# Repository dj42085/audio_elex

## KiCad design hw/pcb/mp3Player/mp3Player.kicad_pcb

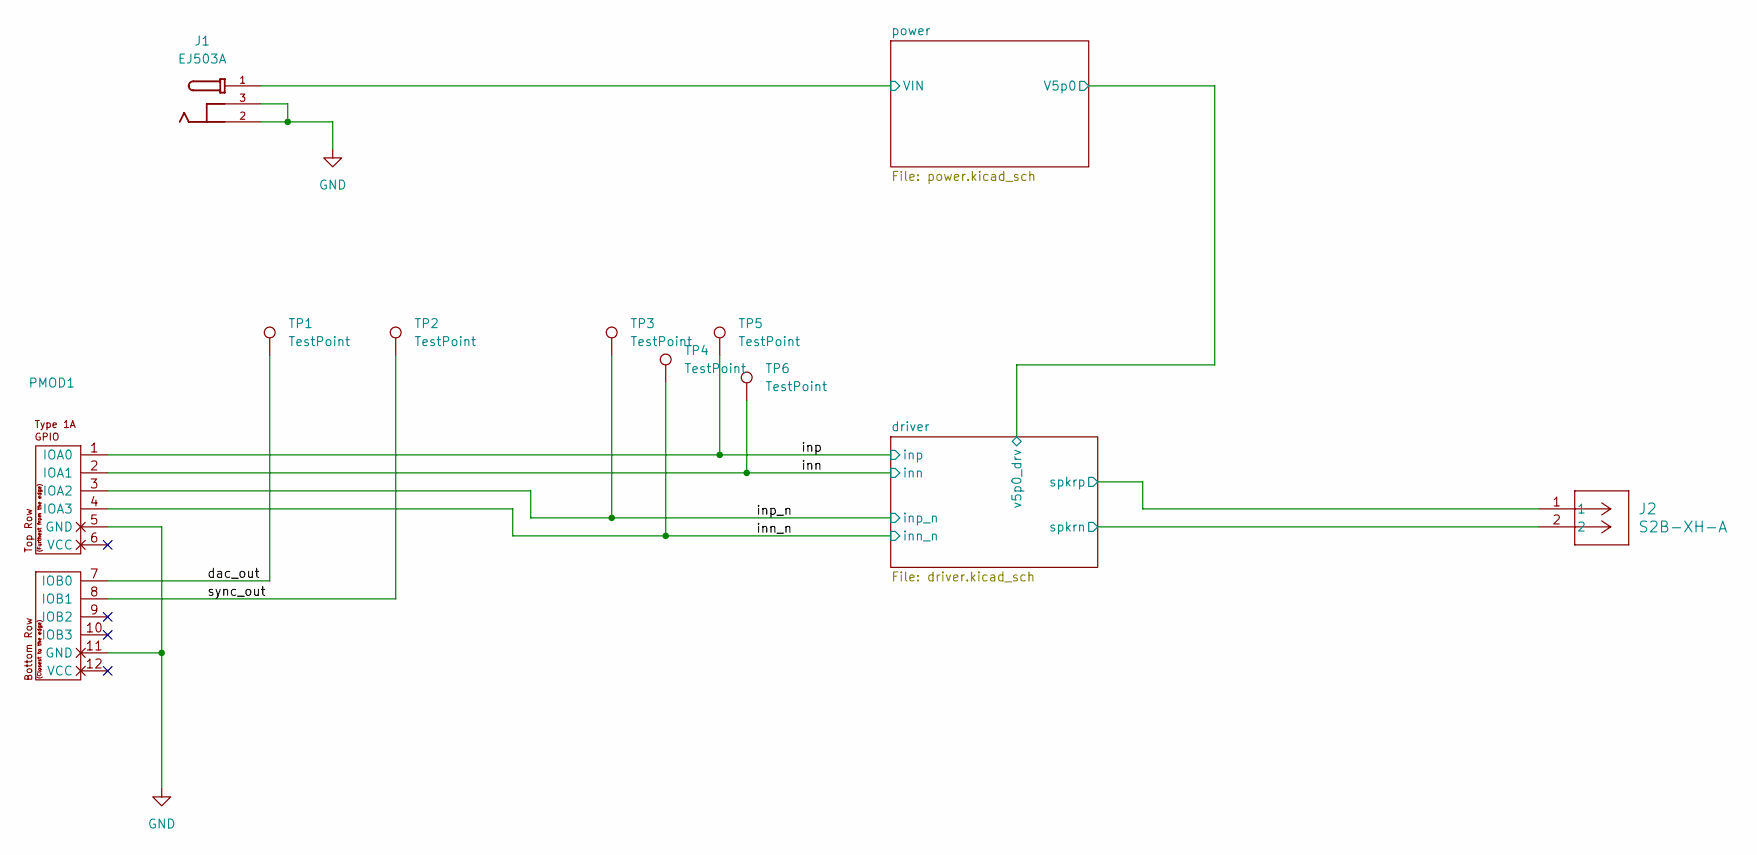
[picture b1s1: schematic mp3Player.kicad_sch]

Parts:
J1: EJ503A; MPD_EJ503A; MPN EJ503A; DigiKey_Part_Number EJ503A-ND
J2: S2B-XH-A; CONN_S2B-XH-A_JST
PMOD1: PMOD-Device-x2-Type-1A-GPIO; pmod_pin_array_6x2
TP1, TP2, TP3, TP4, TP5, TP6: TestPoint; TestPoint_Keystone_5019_Miniature

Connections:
/dac_out: PMOD1.7 (IOB0), TP1.1 (1_1)
/driver/spkrn: J2.2; also elsewhere on the board
/driver/spkrp: J2.1; also elsewhere on the board
/inn: PMOD1.2 (IOA1), TP6.1 (1_1); also elsewhere on the board
/inn_n: PMOD1.4 (IOA3), TP4.1 (1_1); also elsewhere on the board
/inp: PMOD1.1 (IOA0), TP5.1 (1_1); also elsewhere on the board
/inp_n: PMOD1.3 (IOA2), TP3.1 (1_1); also elsewhere on the board
/power/VIN: J1.1; also elsewhere on the board
/sync_out: PMOD1.8 (IOB1), TP2.1 (1_1)
GND: J1.2, J1.3, PMOD1.5 (GND), PMOD1.11 (GND); also elsewhere on the board

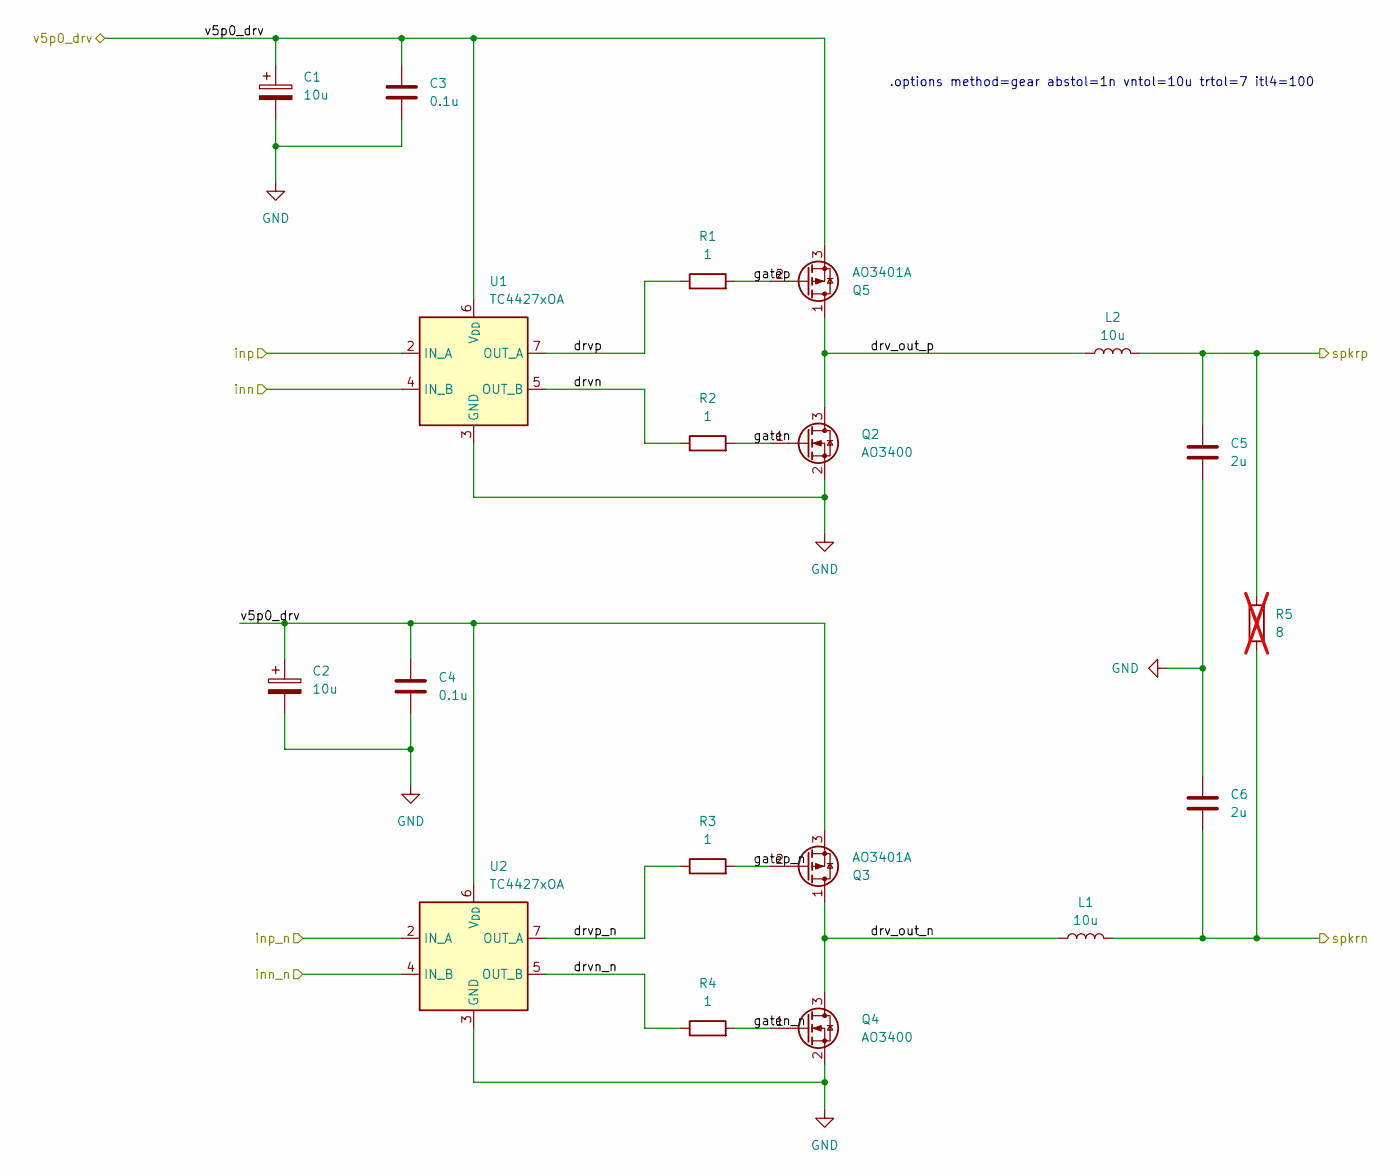
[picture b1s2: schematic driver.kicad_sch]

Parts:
C1, C2: 10u; C_1206_3216Metric
C3, C4: 0.1u; C_0603_1608Metric
C5, C6: 2u; C_0603_1608Metric
L1, L2: 10u; L_Coilcraft_LPS3314
Q2, Q4: AO3400; SOT-23
Q3, Q5: AO3401A; SOT-23
R1, R2, R3, R4: 1; R_0603_1608Metric
R5: 8; not fitted
U1, U2: TC4427xOA; SOIC-8_3.9x4.9mm_P1.27mm

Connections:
/driver/drv_out_n: L1.1, Q3.1 (D), Q4.3 (D)
/driver/drv_out_p: L2.1, Q2.3 (D), Q5.1 (D)
/driver/drvn: R2.1, U1.5 (OUT_B)
/driver/drvn_n: R4.1, U2.5 (OUT_B)
/driver/drvp: R1.1, U1.7 (OUT_A)
/driver/drvp_n: R3.1, U2.7 (OUT_A)
/driver/gaten: Q2.1 (G), R2.2
/driver/gaten_n: Q4.1 (G), R4.2
/driver/gatep: Q5.2 (G), R1.2
/driver/gatep_n: Q3.2 (G), R3.2
/driver/spkrn: C6.2, L1.2, R5.1; also elsewhere on the board
/driver/spkrp: C5.1, L2.2, R5.2; also elsewhere on the board
/driver/v5p0_drv: C1.1, C2.1, C3.1, C4.1, Q3.3 (S), Q5.3 (S), U1.6 (V_{DD}), U2.6 (V_{DD}); also elsewhere on the board
/inn: U1.4 (IN_B); also elsewhere on the board
/inn_n: U2.4 (IN_B); also elsewhere on the board
/inp: U1.2 (IN_A); also elsewhere on the board
/inp_n: U2.2 (IN_A); also elsewhere on the board
GND: C1.2, C2.2, C3.2, C4.2, C5.2, C6.1, Q2.2 (S), Q4.2 (S), U1.3 (GND), U2.3 (GND); also elsewhere on the board

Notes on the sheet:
.options method=gear abstol=1n vntol=10u trtol=7 itl4=100

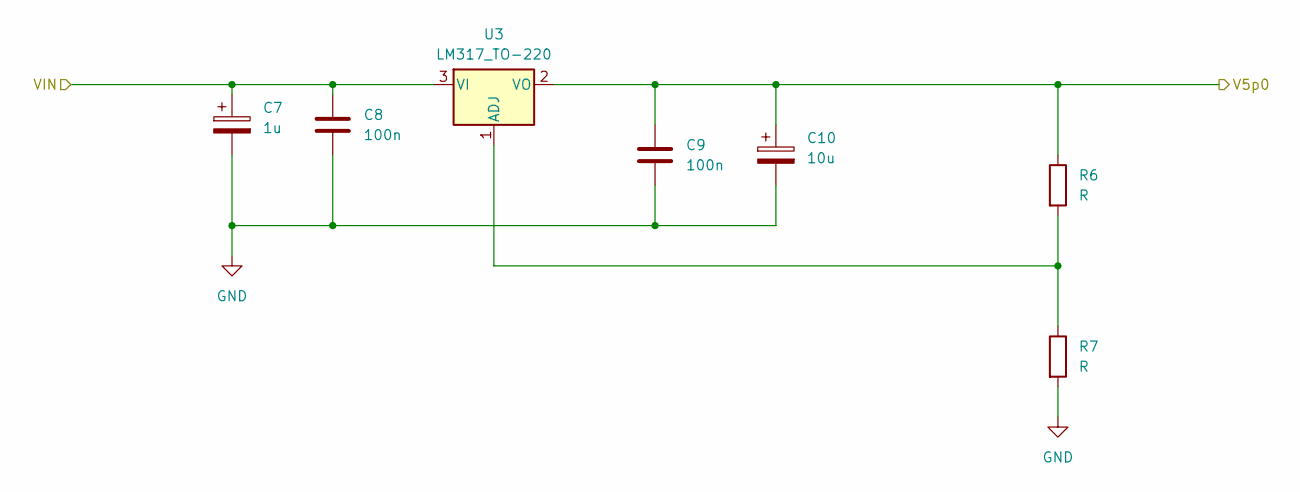
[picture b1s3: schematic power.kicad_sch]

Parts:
C7: 1u; C_0805_2012Metric
C8, C9: 100n; C_0603_1608Metric
C10: 10u; C_0805_2012Metric
R6, R7: R; R_0805_2012Metric
U3: LM317_TO-220; SOT-223

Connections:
/driver/v5p0_drv: C9.1, C10.1, R6.1, U3.2 (VO); also elsewhere on the board
/power/VIN: C7.1, C8.1, U3.3 (VI); also elsewhere on the board
GND: C7.2, C8.2, C9.2, C10.2, R7.2; also elsewhere on the board
unnamed: R6.2, R7.1, U3.1 (ADJ)

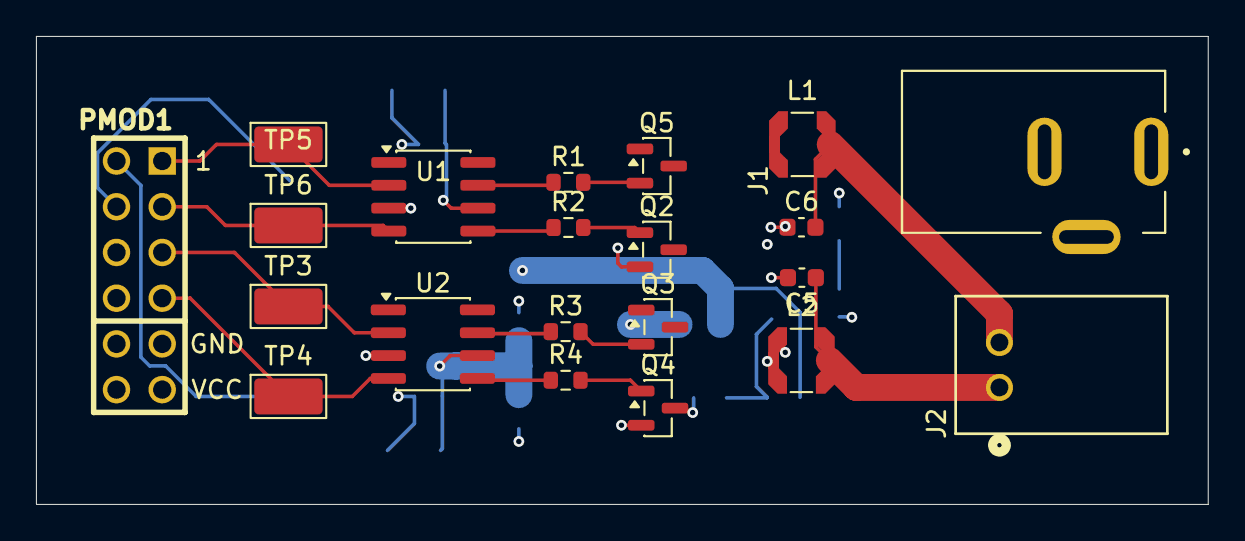
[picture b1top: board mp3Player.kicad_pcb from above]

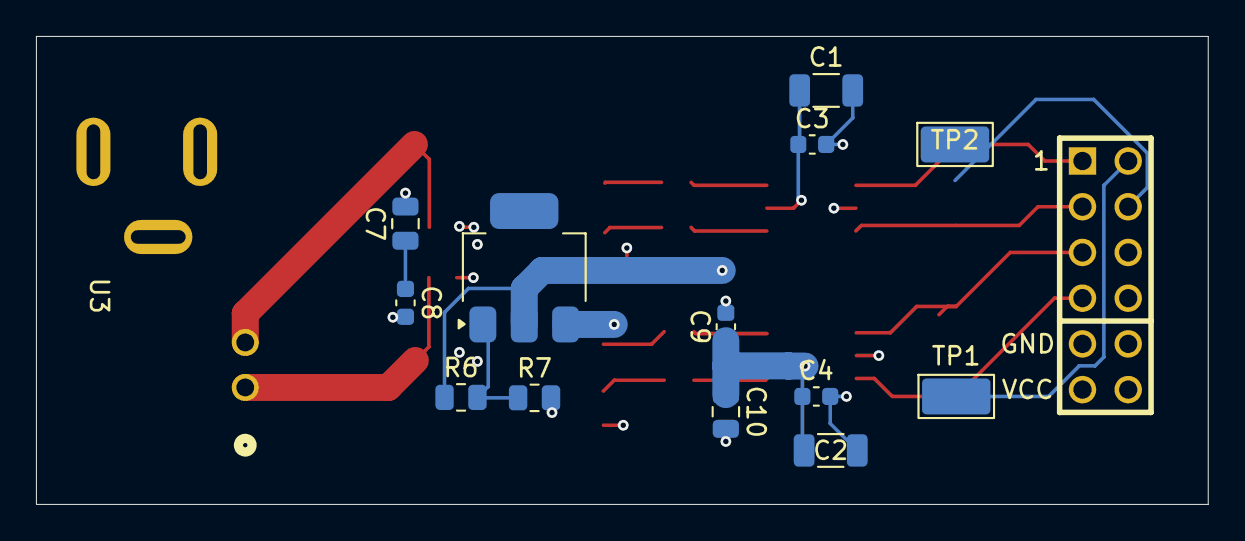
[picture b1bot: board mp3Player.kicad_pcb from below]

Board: 4 copper layers, 65.1 x 26.0 mm, 34 parts (13 on the bottom side), 22 nets.

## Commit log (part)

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2026-03-10 initial code for bluetooth sink
2026-03-10 disabled volume control simulation
2026-03-10 comment to test git integration
